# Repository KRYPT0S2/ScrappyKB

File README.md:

# Scrappy Keyboard

Wireless 68 key split mechanical keyboard running on ZMK firmware.

I majorly made this just for fun and to get back into making hardware, i used KiCad, fusion360 and Ergogen to wire the PCB, make the case and make the PCB respectively, also i made this because my current keyboard sucks TT

---

 **Layout:** 68 keys (total) with an ergonomic thumb cluster.
 
 **Firmware:** Wireless Bluetooth via ZMK firmware.
 
 **Microcontroller:** Dual Pro Micro nRF52840 boards with onboard LiPo charging circuitry.
 
 **Power:** 3.7V 300mAh KP-401230 Li-Po cells with hardware MSK12C02 slide cut-off switches.
 
 **Key Switches:** Gateron Milky Yellow Pro 5-pin linear switches clipped into a 1.5mm top plate.
 
---

## Design & Verification

### Schematic and PCB
* Reversable design
* Key matrix diodes
* B.Cu and F.cu GND copper plane

### Enclosure and Switch Plate
* Modeled in Fusion 360
* Precise cutouts for rear USB-C ports and side power switch actuators

---

## Bill of Materials (BOM)

(Exchange rate: ~₹92.63/USD - ~$82.01 USD total.)

| Sr.no | Name | Footprint | Amt | Source | Unit Price (INR) | Total (INR) |
| :--- | :--- | :--- | :--- | :--- | :--- | :--- |
| 1 | Pro Micro nRF52840 (Type-C / nice!nano v2 pinout) | 24-Pin ProMicro THT | 2 | [Robu.in](https://robu.in/product/promicro-nrf52840-development-board/) | ₹839.00 | ₹1,678.00 |
| 2 | 1N4148 Fast Switching Diodes | DO-35 Axial THT | 68 | [Robu.in](https://robu.in/product/1n4148-1w-zener-diode-pack-of-50/) | ₹1.24 | ₹84.32 |
| 3 | 2.54mm 1×40 Male Breakaway Header Strip | 2.54mm Pitch | 2 | [Robu.in](https://robu.in/product/2-54mm-1x40-pin-male-single-row-straight-short-header-strip-pack-of-3/) | ₹9.00 | ₹18.00 |
| 4 | MSK12C02-HB Horizontal SMD Slide Switch (SPDT) | SMD (C128955) | 2 | [Robu.in](https://robu.in/product/msk12c02-hb-shou-han-horizontal-attachment-50ma-single-pole-double-throw-spdt-12v-10000-times-black-smd-slide-switches-rohs/) | ₹8.00 | ₹16.00 |
| 5 | EasyMech SS 304 M2 × 10mm CSK Philips Screws (25 pcs) | M2 × 10mm | 1 pack | [Robu.in](https://robu.in/product/easymech-ss-304-csk-countersunk-philips-head-m2-x-10-mm-bolt-25-pcs/) | ₹123.00 | ₹123.00 |
| 6 | KP-401230 3.7V 300mAh LiPo Rechargeable Battery (4mm) *(Incl. 18% GST)* | 2-wire leads | 2 | [ElectronicsComp.com](https://www.electronicscomp.com/3.7v-300mah-lipo-battery-model-401230-india) | ₹171.10 | ₹342.20 |
| 7 | Gateron Milky Yellow Pro Linear Switches (5-Pin, 10-pack, 5% off 5+) | MX 5-Pin PCB Mount | 7 packs | [Meckeys.com](https://meckeys.com/shop/accessories/keyboard-accessories/key-switches/gateron-mechanical-pro-switch-5pin/?attribute_pa_switch-variation=pro-milky-yellow) | ₹189.05 | ₹1,323.35 |
| 8 | Blank XDA PBT Keycaps (1u, Set of 5, Black, 10% off 10+) | MX Stem | 14 sets | [Meckeys.com](https://meckeys.com/shop/accessories/keyboard-accessories/keycaps/blank/blank-xda-keycaps-1u/?attribute_pa_keycap-theme=black) | ₹125.10 | ₹1,751.40 |
| 9 | Custom Split Keyboard PCBs (159mm × 110mm, 2-layer) | Custom FR4 (5 pcs) | 1 order | [JLCPCB.com](https://jlcpcb.com/) | ₹1,148.61 | ₹1,148.61 |
| 10 | 3D Printed Case & 1.5mm Switch Plates | PLA / PETG (~120g) | 1 set | printing legion / self | ₹0.00 | ₹0.00 |
| 11 | Shipping & Courier Charges (JLCPCB $11.47 + ElectronicsComp ₹49) | Flat Rate | 1 | Various | ₹1,111.47 | ₹1,111.47 |
| **12** | **Total** | **Full Project Cost** | **—** | **—** | **—** | **₹7,596.35** |

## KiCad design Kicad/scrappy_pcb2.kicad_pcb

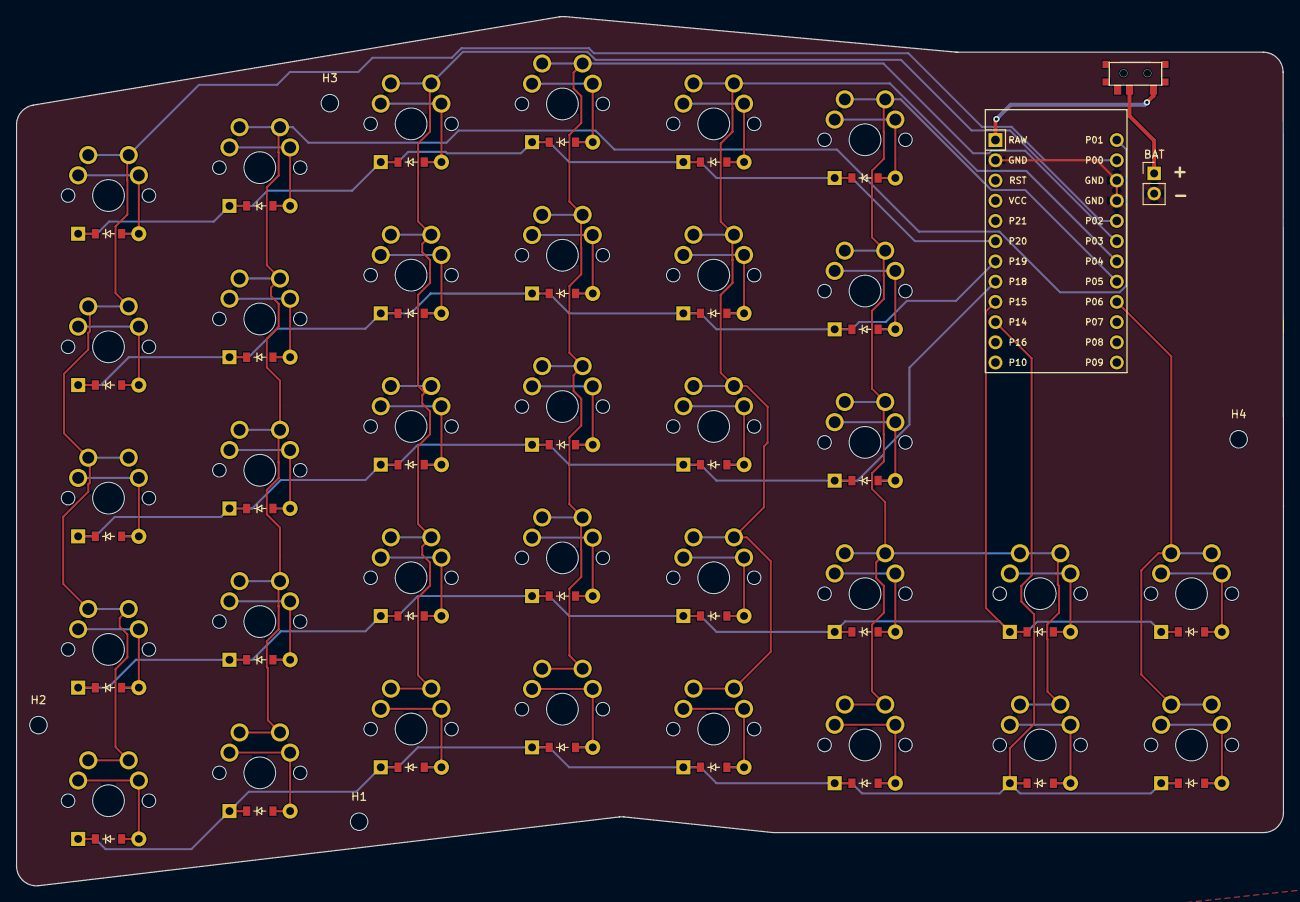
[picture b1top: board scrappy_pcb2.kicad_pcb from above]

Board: 2 copper layers, 159.1 x 109.2 mm, 75 parts (0 on the bottom side), 49 nets.

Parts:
BAT: PinHeader_1x02_P2.54mm_Vertical
D1, D2, D3, D4, D5, D6, D7, D8, D9, D10, D11, D12, D13, D14, D15, D16, D17, D18, D19, D20, D21, D22, D23, D24, D25, D26, D27, D28, D29, D30, D31, D32, D33, D34: ComboDiode
H1, H2, H3, H4: MountingHole_2.2mm_M2
MCU1: ProMicro
S1, S2, S3, S4, S5, S6, S7, S8, S9, S10, S11, S12, S13, S14, S15, S16, S17, S18, S19, S20, S21, S22, S23, S24, S25, S26, S27, S28, S29, S30, S31, S32, S33, S34: MX
T1: SPDT_C128955

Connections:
BPLUS: BAT.+, T1.2
GND: BAT.-, MCU1.2, MCU1.15, MCU1.16
P0: MCU1.14, S1.1, S2.1, S3.1, S4.1, S5.1
P1: MCU1.13, S6.1, S7.1, S8.1, S9.1, S10.1
P2: MCU1.17, S11.1, S12.1, S13.1, S14.1, S15.1
P3: MCU1.18, S16.1, S17.1, S18.1, S19.1, S20.1
P4: MCU1.19, S21.1, S22.1, S23.1, S24.1, S25.1
P5: MCU1.20, S26.1, S27.1, S28.1, S29.1, S30.1, S31.1, S32.1
P6: MCU1.21, S33.1, S34.1
P14: D1.1, D6.1, D11.1, D16.1, D21.1, D26.1, D31.1, D33.1, MCU1.10
P15: D2.1, D7.1, D12.1, D17.1, D22.1, D27.1, D32.1, D34.1, MCU1.9
P18: D3.1, D8.1, D13.1, D18.1, D23.1, D28.1, MCU1.8
P19: D4.1, D9.1, D14.1, D19.1, D24.1, D29.1, MCU1.7
P20: D5.1, D10.1, D15.1, D20.1, D25.1, D30.1, MCU1.6
RAW: MCU1.1, T1.1
c1_r1: D1.2, S1.2
c1_r2: D2.2, S2.2
c1_r3: D3.2, S3.2
c1_r4: D4.2, S4.2
c1_r5: D5.2, S5.2
c2_r1: D6.2, S6.2
c2_r2: D7.2, S7.2
c2_r3: D8.2, S8.2
c2_r4: D9.2, S9.2
c2_r5: D10.2, S10.2
c3_r1: D11.2, S11.2
c3_r2: D12.2, S12.2
c3_r3: D13.2, S13.2
c3_r4: D14.2, S14.2
c3_r5: D15.2, S15.2
c4_r1: D16.2, S16.2
c4_r2: D17.2, S17.2
c4_r3: D18.2, S18.2
c4_r4: D19.2, S19.2
c4_r5: D20.2, S20.2
c5_r1: D21.2, S21.2
c5_r2: D22.2, S22.2
c5_r3: D23.2, S23.2
c5_r4: D24.2, S24.2
c5_r5: D25.2, S25.2
c6_r1: D26.2, S26.2
c6_r2: D27.2, S27.2
c6_r3: D28.2, S28.2
c6_r4: D29.2, S29.2
c6_r5: D30.2, S30.2
t1_b1: D31.2, S31.2
t1_b2: D32.2, S32.2
t2_b1: D33.2, S33.2
t2_b2: D34.2, S34.2
